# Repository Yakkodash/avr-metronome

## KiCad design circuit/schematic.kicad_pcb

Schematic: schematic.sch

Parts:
C1: 100n; C_0603_1608Metric
C2: 0.47u; C_0603_1608Metric_Pad1.05x0.95mm_HandSolder
C3, C10, C11: 220u; CP_Radial_D8.0mm_P3.50mm
C4, C6, C13, C14, C15, C16, C17, C18, C19: 0.1u; C_0603_1608Metric_Pad1.05x0.95mm_HandSolder
C5: 100u; CP_Radial_D8.0mm_P3.50mm
C7: 470p; C_0603_1608Metric_Pad1.05x0.95mm_HandSolder
C8, C9: 22p; C_0603_1608Metric_Pad1.05x0.95mm_HandSolder
C12: 470u; CP_Radial_D8.0mm_P3.50mm
D1: 1N4007; D_DO-41_SOD81_P7.62mm_Horizontal
D2, D3, D4: LED; LED_D3.0mm
D5: 1N5819; D_DO-41_SOD81_P7.62mm_Horizontal
H1, H2, H3, H4: MountingHole; MountingHole_3.2mm_M3
J1: Conn_01x02_Male; PinHeader_1x02_P2.54mm_Vertical
J2: Conn_01x05_Male; PinHeader_1x05_P2.54mm_Vertical
J3: Conn_01x02_Female; PinHeader_1x02_P2.54mm_Vertical
J4: AudioJack3_SwitchTR; PinHeader_1x05_P2.54mm_Vertical
L1: 220u; L_10.4x10.4_H4.8
R1, R9: 5k; R_0603_1608Metric_Pad1.05x0.95mm_HandSolder
R2: 150; R_0603_1608Metric_Pad1.05x0.95mm_HandSolder
R3: 0.33; R_Axial_DIN0204_L3.6mm_D1.6mm_P7.62mm_Horizontal
R4, R5, R6: 510; R_0603_1608Metric_Pad1.05x0.95mm_HandSolder
R7: 20k; R_0603_1608Metric_Pad1.05x0.95mm_HandSolder
R8: 1.2k; R_0603_1608Metric_Pad1.05x0.95mm_HandSolder
R10: 3.6k; R_0603_1608Metric_Pad1.05x0.95mm_HandSolder
R11, R12: 4.7k; R_0603_1608Metric_Pad1.05x0.95mm_HandSolder
R13: 330; R_0603_1608Metric_Pad1.05x0.95mm_HandSolder
R14, R15, R16, R17, R18, R19, R20, R21, R22, R23, R24, R25: 10k; R_0603_1608Metric_Pad1.05x0.95mm_HandSolder
RV1: R_POT_Dual; Potentiometer_Alps_RK09L_Double_Vertical
RV2: 20k; Potentiometer_Bourns_3314G_Vertical
SW1: Rotary_Encoder_Switch; RotaryEncoder_Alps_EC11E-Switch_Vertical_H20mm_CircularMoun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
SW2: SW_Push; PinHeader_1x02_P2.54mm_Vertical
SW3, SW4: SW_Push; SW_PUSH_6mm_H5mm
U1: ATmega328-AU; TQFP-32_7x7mm_P0.8mm
U2: SSM2211S; SOIC-8_3.9x4.9mm_P1.27mm
U3: MC33063AD; SOIC-8_3.9x4.9mm_P1.27mm
U4: STP08CP05; SOIC-16_3.9x9.9mm_P1.27mm
U5: 74HC14; SOIC-14_3.9x8.7mm_P1.27mm
U6: CC56-12SRWA; CA56-12SRWA
Y1: 16M; Crystal_SMD_5032-2Pin_5.0x3.2mm_HandSoldering

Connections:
+5V: C3.1, C4.2, C12.1, C13.1, J2.2, L1.2, R1.2, R9.1, R10.1, R14.1, R15.1, R16.1, R17.1, R18.1, R19.1, U1.4, U1.6, U1.18, U2.6, U4.4, U4.16, U5.14 (VCC)
+9V: C5.1, D1.1 (K), R3.2, U3.6
AMP_SHUTDOWN: R1.1, U1.28, U2.1
BUTTON0: U1.1, U5.2
BUTTON1: U1.32, U5.4
BUTTON2: U1.31, U5.6
DIG0: U1.23, U6.12 (CC1)
DIG1: U1.24, U6.9 (CC2)
DIG2: U1.25, U6.8 (CC3)
DIG3: U1.26, U6.6 (CC4)
ENC_A: U1.13, U5.8
ENC_B: U1.12, U5.10
ENC_BUTTON: U1.11, U5.12
GND: C1.2, C3.2, C4.1, C5.2, C6.2, C7.2, C8.1, C9.2, C12.2, C13.2, C14.2, C15.2, C16.2, C17.2, C18.2, C19.2, D2.1 (K), D3.1 (K), D4.1 (K), D5.2, J1.1, J2.1, J4.S, R8.1, R11.2, R12.2, RV1.1, RV1.4, RV2.2, RV2.3, SW1.C, SW1.MP, SW1.S1, SW2.1, SW3.1, SW4.1, U1.3, U1.5, U1.21, U2.7, U3.4, U4.1, U4.13, U5.7 (GND)
NRST: J2.3, R9.2, U1.29
unnamed: C1.1, U1.20
unnamed: C2.1, R2.2
unnamed: C6.1, U2.2, U2.3
unnamed: C7.1, U3.3
unnamed: C8.2, U1.7, Y1.1
unnamed: C9.1, U1.8, Y1.2
unnamed: C10.1, R7.1, U2.5
unnamed: C10.2, RV1.3
unnamed: C11.1, U2.8
unnamed: C11.2, RV1.6
unnamed: C14.1, R20.2, U5.11
unnamed: C15.1, R21.1, U5.13
unnamed: C16.1, R22.1, U5.9
unnamed: C17.1, R23.1, U5.1
unnamed: C18.1, R24.1, U5.3
unnamed: C19.1, R25.2, U5.5
unnamed: D1.2 (A), J1.2
unnamed: D2.2 (A), R4.2
unnamed: D3.2 (A), R5.1
unnamed: D4.2 (A), R6.2
unnamed: D5.1, L1.1, U3.2
unnamed: J3.1, J4.RN
unnamed: J3.2, J4.TN
unnamed: J4.R, R12.1, RV1.5
unnamed: J4.T, R11.1, RV1.2
unnamed: R2.1, R7.2, U2.4
unnamed: R3.1, U3.1, U3.7, U3.8
unnamed: R4.1, U1.30
unnamed: R5.2, U1.9
unnamed: R6.1, U1.2
unnamed: R8.2, R10.2, U3.5
unnamed: R13.1, U4.15
unnamed: R13.2, RV2.1
unnamed: R14.2, R20.1, SW1.A
unnamed: R15.2, R21.2, SW1.S2
unnamed: R16.2, R22.2, SW1.B
unnamed: R17.2, R23.2, SW2.2
unnamed: R18.2, R24.2, SW3.2
unnamed: R19.2, R25.1, SW4.2
unnamed: U4.5, U6.11 (a)
unnamed: U4.6, U6.7 (b)
unnamed: U4.7, U6.4 (c)
unnamed: U4.8, U6.2 (d)
unnamed: U4.9, U6.1 (e)
unnamed: U4.10, U6.10 (f)
unnamed: U4.11, U6.5 (g)
unnamed: U4.12, U6.3 (DPX)
SOUND_OUT: C2.2, U1.10
SPI_MISO: J2.4, U1.16
SPI_MOSI: U1.15, U4.2
SPI_SCK: J2.5, U1.17, U4.3

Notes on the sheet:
27 1.2
MIDI OUT?
Speaker
3 1
6 4

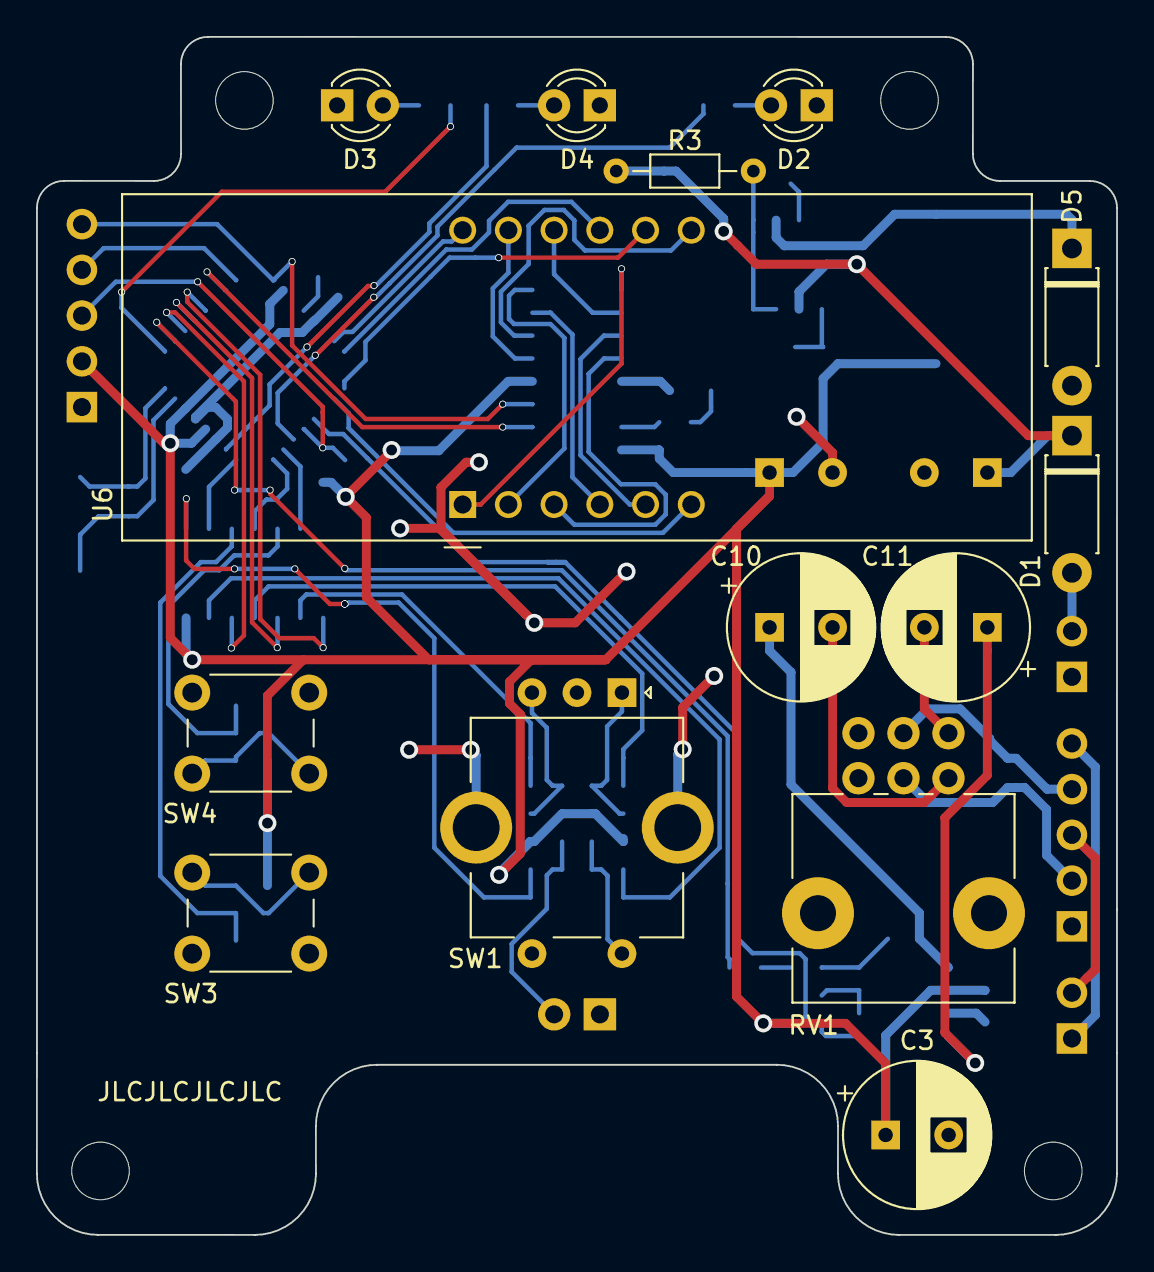
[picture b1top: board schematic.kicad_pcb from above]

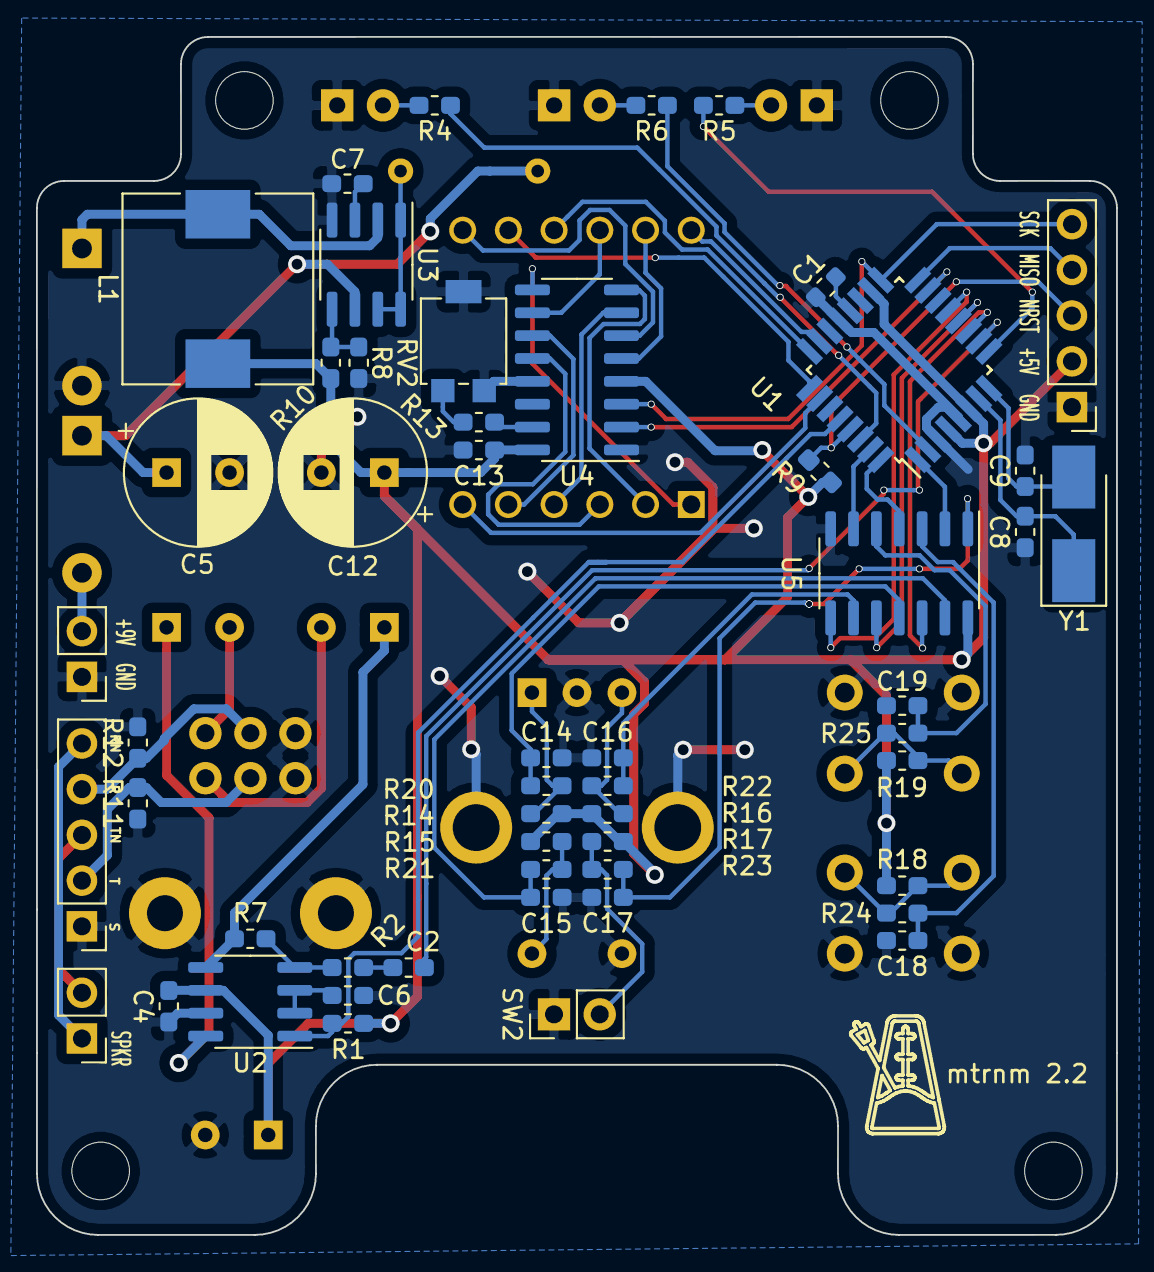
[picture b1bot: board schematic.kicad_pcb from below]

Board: 2 copper layers, 60.0 x 66.6 mm, 71 parts (53 on the bottom side), 66 nets.

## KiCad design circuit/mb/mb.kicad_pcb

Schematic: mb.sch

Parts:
BT1: 9V; PinHeader_1x02_P2.54mm_Vertical
C1, C2: 22p; C_Disc_D3.8mm_W2.6mm_P2.50mm
C3: 47u; CP_Radial_D4.0mm_P2.00mm
C4: 100u; CP_Radial_D4.0mm_P2.00mm
C5: 2200u; CP_Axial_L29.0mm_D13.0mm_P35.00mm_Horizontal
D1: 1N4001; D_DO-35_SOD27_P7.62mm_Horizontal
J1, J10: Conn_01x03_Male; PinHeader_1x03_P2.54mm_Vertical
J2: Conn_01x02_Male; PinHeader_1x02_P2.54mm_Vertical
J3: Barrel_Jack_Switch; PinHeader_1x03_P2.54mm_Vertical
J4: Conn_02x03_Odd_Even; PinHeader_2x03_P2.54mm_Vertical
J5, J6, J7: Conn_01x04_Male; PinHeader_1x04_P2.54mm_Vertical
J8, J9: Conn_01x05_Male; PinHeader_1x05_P2.54mm_Vertical
LS1: Speaker; PinHeader_1x02_P2.54mm_Vertical
Q1: BC337; TO-92_Inline_Wide
R1: 2.2k; R_Axial_DIN0204_L3.6mm_D1.6mm_P7.62mm_Horizontal
R2, R3: 100k; R_Axial_DIN0204_L3.6mm_D1.6mm_P7.62mm_Horizontal
R4: 10; R_Axial_DIN0204_L3.6mm_D1.6mm_P7.62mm_Horizontal
R5: 1k; R_Axial_DIN0204_L3.6mm_D1.6mm_P7.62mm_Horizontal
R6: 10k; R_Axial_DIN0204_L3.6mm_D1.6mm_P7.62mm_Horizontal
R7, R13: 0; R_Axial_DIN0204_L3.6mm_D1.6mm_P5.08mm_Horizontal
R8, R9, R10, R14, R16, R19, R22, R24: 0; R_Axial_DIN0204_L3.6mm_D1.6mm_P7.62mm_Horizontal
R11, R12, R15, R17, R18, R20, R21, R25: 0; R_Axial_DIN0207_L6.3mm_D2.5mm_P10.16mm_Horizontal
R23: 0; R_Axial_DIN0309_L9.0mm_D3.2mm_P20.32mm_Horizontal
R26: 0; R_Axial_DIN0309_L9.0mm_D3.2mm_P25.40mm_Horizontal
SW1, SW2: SW_SPDT; PinHeader_1x03_P2.54mm_Vertical
U1: ATmega328P-PU; DIP-28_W7.62mm_Socket
U2: L7805; TO-220-3_Vertical
Y1: 16M; Resonator-2Pin_W10.0mm_H5.0mm

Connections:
+5V: C5.1, J4.2, J8.5, J9.5, J10.1, R4.2, R10.1, R10.2, R11.2, R14.1, R14.2, R16.1, R16.2, U1.20 (AVCC), U1.21 (AREF), U2.3 (OUT)
+9V: C4.1, SW2.2 (B), U2.1 (IN)
BUTTON0: J5.3, U1.5 (PD3)
BUTTON1: J5.2, U1.4 (PD2)
BUTTON2: J5.1, R13.1
DIG0: J6.3, U1.24 (PC1)
DIG1: J6.2, U1.25 (PC2)
DIG2: J6.1, U1.26 (PC3)
DIG3: J6.4, U1.23 (PC0)
ENC_A: J8.2, U1.15 (PB1)
ENC_B: J8.3, U1.14 (PB0)
ENC_BUTTON: J5.4, R12.1
GND: BT1.2 (-), C1.1, C2.1, C3.2, C4.2, C5.2, J3.1, J4.6, J7.4, J8.4, J9.2, Q1.3 (E), R3.2, R6.1, R17.1, R17.2, R19.1, R19.2, R20.1, R20.2, R21.1, R21.2, SW1.1 (A), U1.8 (GND), U1.22 (GND), U2.2 (GND)
LED0: R22.1, U1.2 (PD0)
LED1: R15.1, R24.1
LED2: R26.1, U1.11 (PD5)
NRST: J4.5, J10.2, R7.1, R7.2, U1.1 (~RESET~/PC6)
unnamed: BT1.1 (+), J3.3
unnamed: C1.2, U1.9 (XTAL1/PB6), Y1.1
unnamed: C2.2, U1.10 (XTAL2/PB7), Y1.2
unnamed: C3.1, R5.1
unnamed: D1.1, J1.1, J2.1, LS1.1, Q1.1 (C), R2.1
unnamed: D1.2, J1.2, J2.2, SW1.3 (C)
unnamed: J1.3, R4.1
unnamed: J3.2, SW2.3 (C)
unnamed: J7.1, R22.2
unnamed: J7.2, R24.2
unnamed: J7.3, R25.1
unnamed: J9.3, R9.1
unnamed: J10.3, R6.2
unnamed: LS1.2, SW1.2 (B)
unnamed: Q1.2 (B), R1.1, R2.2, R3.1
unnamed: R8.2, U1.17 (PB3)
unnamed: R11.1, U1.7 (VCC)
unnamed: R12.2, U1.13 (PD7)
unnamed: R13.2, U1.3 (PD1)
unnamed: R15.2, U1.6 (PD4)
unnamed: R5.2, R18.1
unnamed: R18.2, U1.28 (PC5)
unnamed: R23.2, U1.27 (PC4)
unnamed: R25.2, R26.2
SOUND_OUT: R1.2, U1.12 (PD6)
SPI_MISO: J4.1, U1.18 (PB4)
SPI_MOSI: J4.4, J9.1, R8.1
SPI_NSS: R9.2, U1.16 (PB2)
SPI_SCK: J4.3, J9.4, U1.19 (PB5)
SWITCH0: J8.1, R23.1

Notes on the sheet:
Audio jack Must be isolated from the chassis

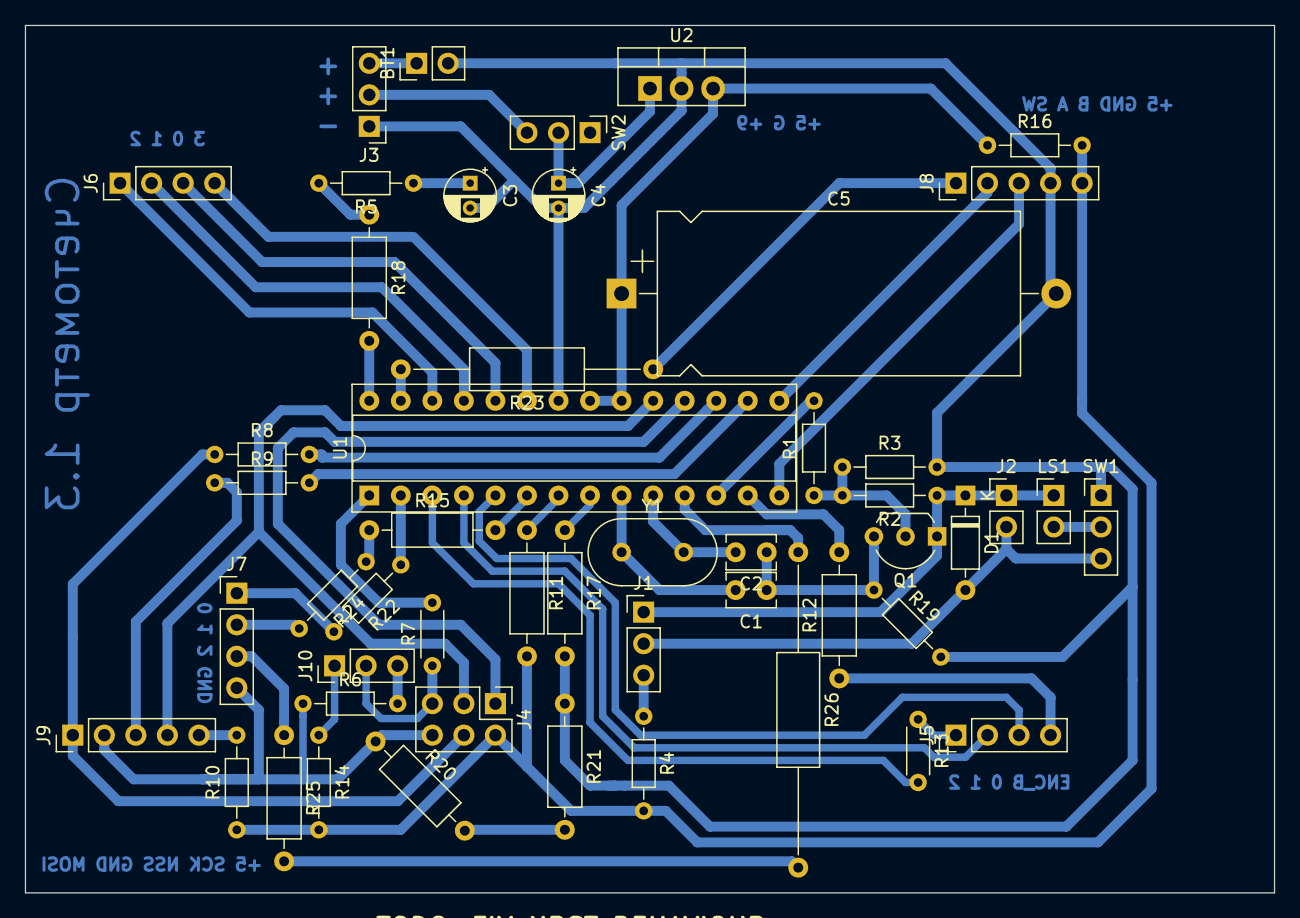
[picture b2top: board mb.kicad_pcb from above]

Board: 2 copper layers, 100.6 x 69.9 mm, 50 parts (0 on the bottom side), 47 nets.

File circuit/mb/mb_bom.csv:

"Позиция";"Обозначение";"Корпус";"Количество";"Значение";"Поставщик и справка";
1;"R8,R9,R16,R10,R19,R22,R24,R14";"R_Axial_DIN0204_L3.6mm_D1.6mm_P7.62mm_Horizontal";8;"0";;;
2;"U1";"DIP-28_W7.62mm_Socket";1;"ATmega328P-PU";;;
3;"J4";"PinHeader_2x03_P2.54mm_Vertical";1;"Conn_02x03_Odd_Even";;;
4;"SW2,SW1";"PinHeader_1x03_P2.54mm_Vertical";2;"SW_SPDT";;;
5;"Y1";"Resonator-2Pin_W10.0mm_H5.0mm";1;"16M";;;
6;"Q1";"TO-92_Inline_Wide";1;"BC337";;;
7;"BT1";"PinHeader_1x02_P2.54mm_Vertical";1;"9V";;;
8;"J1,J10";"PinHeader_1x03_P2.54mm_Vertical";2;"Conn_01x03_Male";;;
9;"J2";"PinHeader_1x02_P2.54mm_Vertical";1;"Conn_01x02_Male";;;
10;"J3";"PinHeader_1x03_P2.54mm_Vertical";1;"Barrel_Jack_Switch";;;
11;"J5,J6,J7";"PinHeader_1x04_P2.54mm_Vertical";3;"Conn_01x04_Male";;;
12;"J8,J9";"PinHeader_1x05_P2.54mm_Vertical";2;"Conn_01x05_Male";;;
13;"R1";"R_Axial_DIN0204_L3.6mm_D1.6mm_P7.62mm_Horizontal";1;"2.2k";;;
14;"R2,R3";"R_Axial_DIN0204_L3.6mm_D1.6mm_P7.62mm_Horizontal";2;"100k";;;
15;"R4";"R_Axial_DIN0204_L3.6mm_D1.6mm_P7.62mm_Horizontal";1;"10";;;
16;"R5";"R_Axial_DIN0204_L3.6mm_D1.6mm_P7.62mm_Horizontal";1;"1k";;;
17;"LS1";"PinHeader_1x02_P2.54mm_Vertical";1;"Speaker";;;
18;"U2";"TO-220-3_Vertical";1;"L7805";;;
19;"R6";"R_Axial_DIN0204_L3.6mm_D1.6mm_P7.62mm_Horizontal";1;"10k";;;
20;"R11,R18,R12,R15,R17,R20,R21,R25";"R_Axial_DIN0207_L6.3mm_D2.5mm_P10.16mm_Horizontal";8;"0";;;
21;"D1";"D_DO-35_SOD27_P7.62mm_Horizontal";1;"1N4001";;;
22;"R23";"R_Axial_DIN0309_L9.0mm_D3.2mm_P20.32mm_Horizontal";1;"0";;;
23;"C5";"CP_Axial_L29.0mm_D13.0mm_P35.00mm_Horizontal";1;"2200u";;;
24;"C3";"CP_Radial_D4.0mm_P2.00mm";1;"47u";;;
25;"C4";"CP_Radial_D4.0mm_P2.00mm";1;"100u";;;
26;"C1,C2";"C_Disc_D3.8mm_W2.6mm_P2.50mm";2;"22p";;;
27;"R7,R13";"R_Axial_DIN0204_L3.6mm_D1.6mm_P5.08mm_Horizontal";2;"0";;;
28;"R26";"R_Axial_DIN0309_L9.0mm_D3.2mm_P25.40mm_Horizontal";1;"0";;;

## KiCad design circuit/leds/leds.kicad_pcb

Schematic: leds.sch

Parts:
D1, D2, D3: LED; LED_D5.0mm
J1: Conn_01x04_Female; PinHeader_1x04_P2.54mm_Vertical
R1, R2, R3: 510; R_Axial_DIN0204_L3.6mm_D1.6mm_P7.62mm_Horizontal

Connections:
GND: D1.1 (K), D2.1 (K), D3.1 (K), J1.4
LED0: J1.1, R1.2
LED1: J1.2, R2.2
LED2: J1.3, R3.2
unnamed: D1.2 (A), R1.1
unnamed: D2.2 (A), R2.1
unnamed: D3.2 (A), R3.1

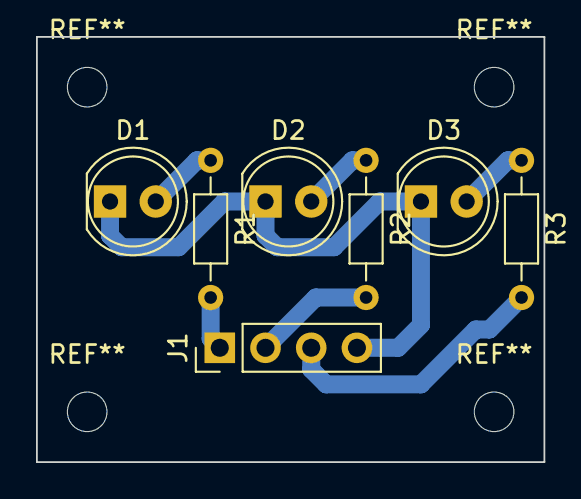
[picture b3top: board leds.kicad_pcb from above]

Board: 2 copper layers, 28.2 x 23.6 mm, 7 parts (0 on the bottom side), 7 nets.

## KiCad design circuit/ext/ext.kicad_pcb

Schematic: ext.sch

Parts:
C1, C2, C3, C4, C5, C6: 0.1u; C_Disc_D4.3mm_W1.9mm_P5.00mm
J1: Conn_01x04_Female; PinSocket_1x04_P2.54mm_Vertical
J2: Conn_01x03_Female; PinSocket_1x03_P2.54mm_Vertical
J3: Conn_01x05_Female; PinSocket_1x05_P2.54mm_Vertical
R1, R2, R3, R4, R5, R6, R7, R8, R9, R10, R11, R12: 10k; R_Axial_DIN0204_L3.6mm_D1.6mm_P7.62mm_Horizontal
R13, R14, R16: 0; R_Axial_DIN0204_L3.6mm_D1.6mm_P5.08mm_Horizontal
R15: 0; R_Axial_DIN0207_L6.3mm_D2.5mm_P15.24mm_Horizontal
R17: 0; R_Axial_DIN0207_L6.3mm_D2.5mm_P7.62mm_Horizontal
R18, R19, R20, R21, R22: 0; R_Axial_DIN0204_L3.6mm_D1.6mm_P7.62mm_Horizontal
RV1: 25k; Potentiometer_Alps_RK09K_Single_Vertical
SW1: Rotary_Encoder_Switch; RotaryEncoder_Alps_EC11E-Switch_Vertical_H20mm_CircularMoun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
SW2, SW4: SW_Push; SW_PUSH_6mm_H5mm
SW3: SW_Push; PinSocket_1x02_P2.54mm_Vertical
SW5: SW_SPDT; PinSocket_1x03_P2.54mm_Vertical
U1: 74HC14; DIP-14_W7.62mm_Socket

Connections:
+5V: J3.1, R1.1, R2.1, R3.1, R4.1, R5.1, R6.1, R13.1, R13.2, R14.1, R14.2, R16.1, R16.2, SW5.3 (C), U1.14 (VCC)
BUTTON0: J1.3, U1.8
BUTTON1: J1.2, U1.10
BUTTON2: J1.1, U1.12
ENC_A: J3.4, R19.2
ENC_B: J3.3, U1.4
ENC_BUTTON: J1.4, U1.6
GND: C1.2, C2.2, C3.2, C4.1, C5.2, C6.2, J3.2, SW1.C, SW1.S1, SW2.1, SW3.1, SW4.1, SW5.1 (A), U1.7 (GND)
unnamed: C1.1, R11.2, U1.1
unnamed: C2.1, R12.1, R22.2
unnamed: C3.1, R7.1, U1.3
unnamed: C4.2, R8.2, R20.2
unnamed: C5.1, R9.1, R17.2
unnamed: C6.1, R10.1, R18.2
unnamed: J2.1, RV1.1
unnamed: J2.2, RV1.2
unnamed: J2.3, RV1.3
unnamed: R1.2, R11.1, SW1.A
unnamed: R3.2, R7.2, SW1.B
unnamed: R4.2, R8.1, SW2.2
unnamed: R5.2, R9.2, SW3.2
unnamed: R6.2, R10.2, SW4.2
unnamed: R2.2, R12.2, SW1.S2
unnamed: R15.1, SW5.2 (B)
unnamed: R17.1, U1.11
unnamed: R18.1, U1.13
unnamed: R19.1, U1.2
unnamed: R20.1, R21.2
unnamed: R21.1, U1.9
unnamed: R22.1, U1.5
SWITCH0: J3.5, R15.2

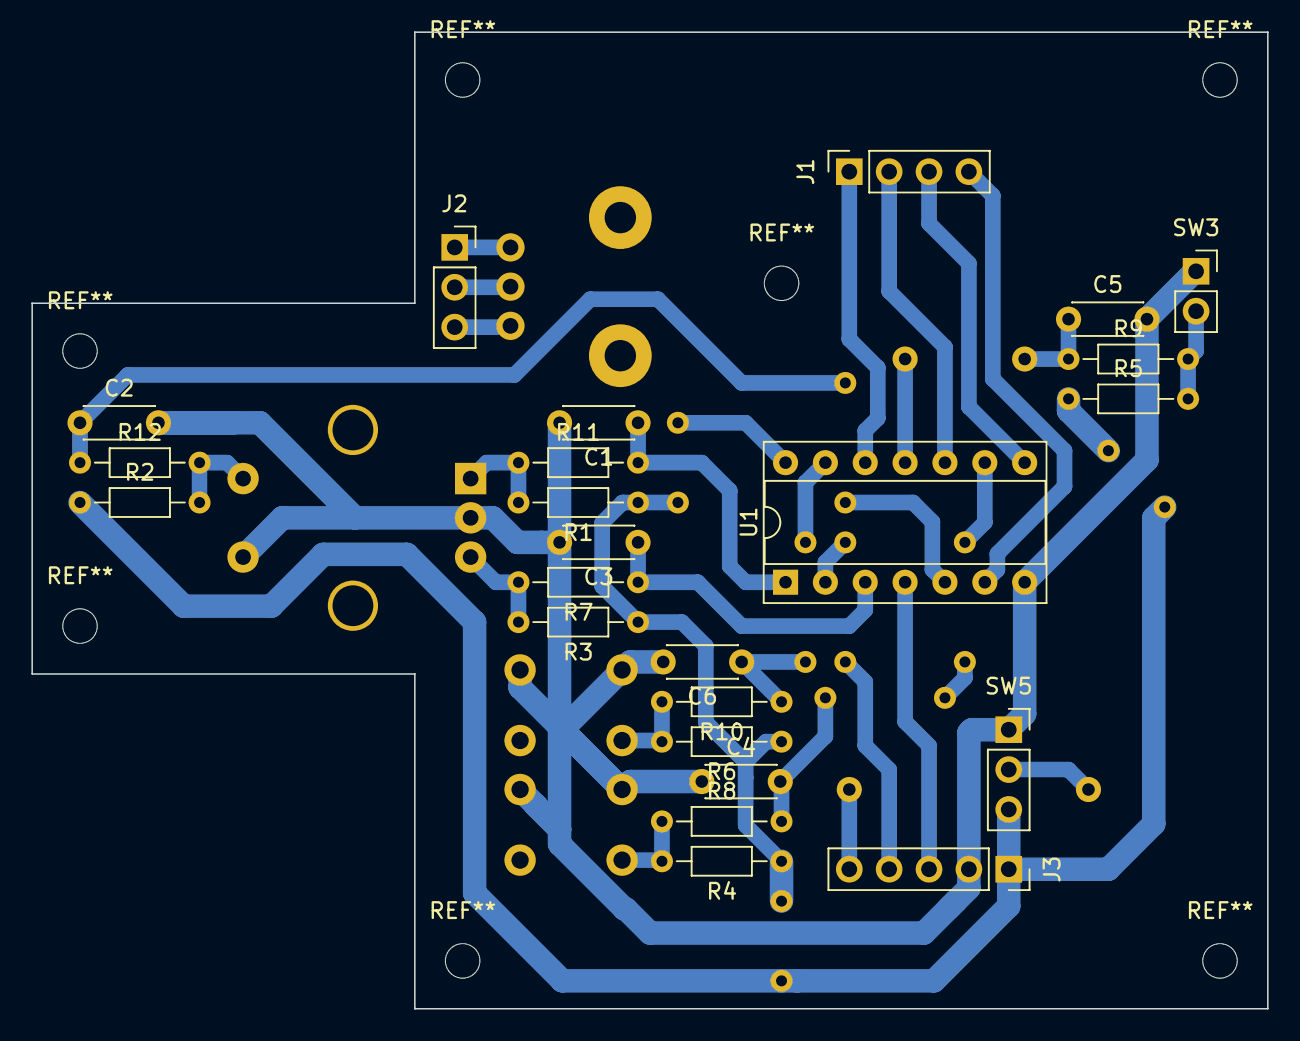
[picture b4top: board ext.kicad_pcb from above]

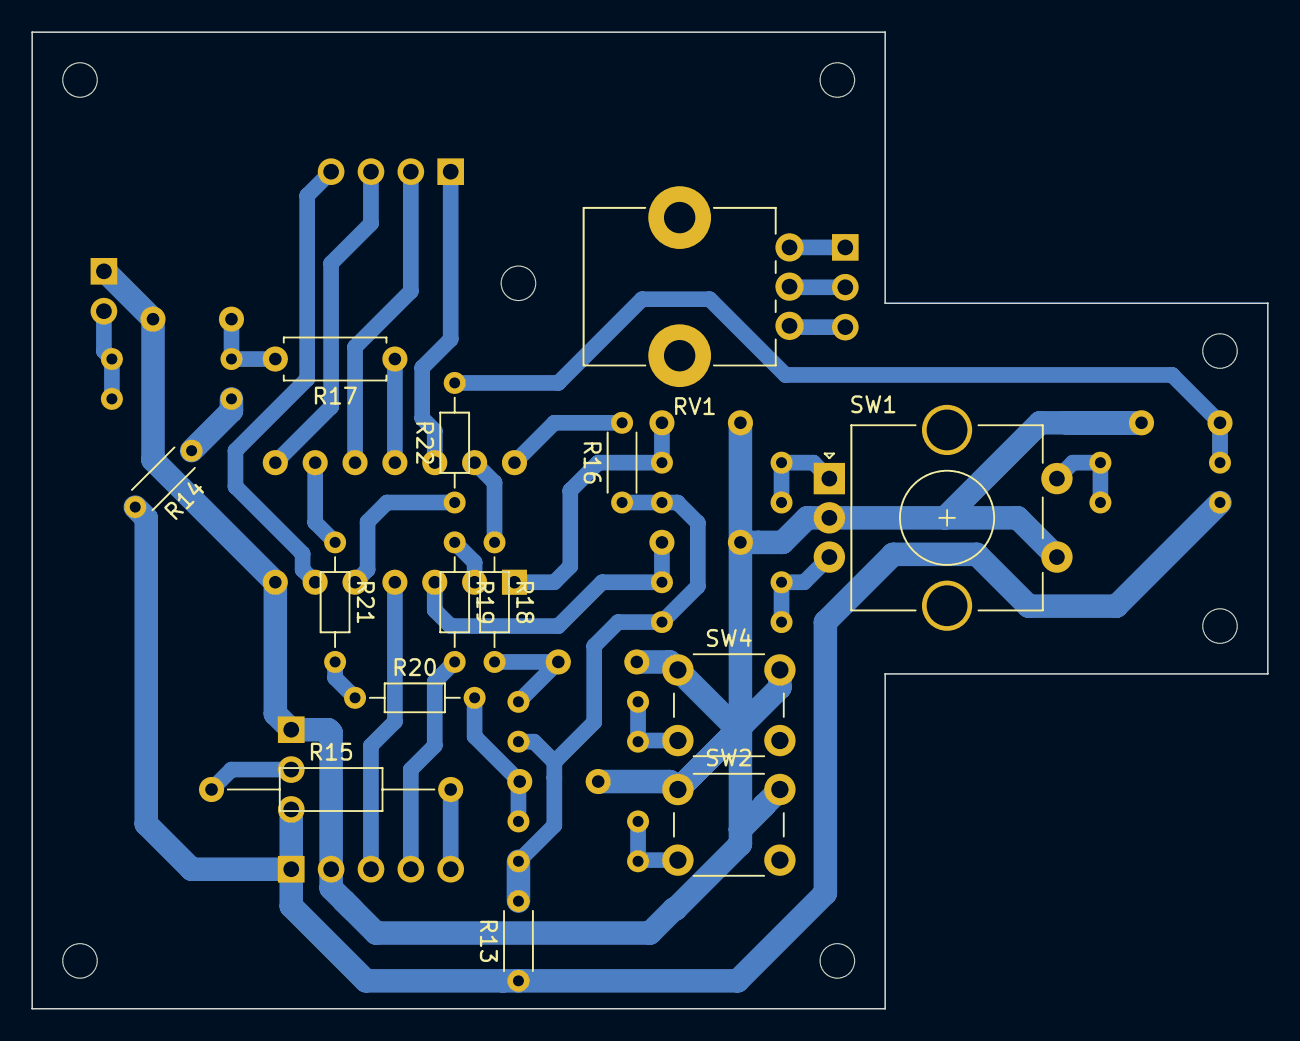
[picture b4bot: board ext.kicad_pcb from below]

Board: 2 copper layers, 78.7 x 62.2 mm, 38 parts (14 on the bottom side), 31 nets.

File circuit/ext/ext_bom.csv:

"Позиция";"Обозначение";"Корпус";"Количество";"Значение";"Поставщик и справка";
1;"REF**,REF**,REF**,REF**,REF**,REF**,REF**";"MountingHole_2.2mm_M2";7;"MountingHole_2.2mm_M2";;;
2;"C1,C2,C3,C4,C5,C6";"C_Disc_D4.3mm_W1.9mm_P5.00mm";6;"0.1u";;;
3;"J3";"PinSocket_1x05_P2.54mm_Vertical";1;"Conn_01x05_Female";;;
4;"R1,R2,R3,R4,R5,R6,R7,R8,R9,R10,R11,R12";"R_Axial_DIN0204_L3.6mm_D1.6mm_P7.62mm_Horizontal";12;"10k";;;
5;"U1";"DIP-14_W7.62mm_Socket";1;"74HC14";;;
6;"RV1";"Potentiometer_Alps_RK09K_Single_Vertical";1;"25k";;;
7;"SW1";"RotaryEncoder_Alps_EC11E-Switch_Vertical_H20mm_CircularMountingHoles";1;"Rotary_Encoder_Switch";;;
8;"SW2,SW4";"SW_PUSH_6mm_H5mm";2;"SW_Push";;;
9;"SW3";"PinSocket_1x02_P2.54mm_Vertical";1;"SW_Push";;;
10;"SW5";"PinSocket_1x03_P2.54mm_Vertical";1;"SW_SPDT";;;
11;"J2";"PinSocket_1x03_P2.54mm_Vertical";1;"Conn_01x03_Female";;;
12;"R13,R14,R16";"R_Axial_DIN0204_L3.6mm_D1.6mm_P5.08mm_Horizontal";3;"0";;;
13;"R18,R19,R20,R21,R22";"R_Axial_DIN0204_L3.6mm_D1.6mm_P7.62mm_Horizontal";5;"0";;;
14;"R17";"R_Axial_DIN0207_L6.3mm_D2.5mm_P7.62mm_Horizontal";1;"0";;;
15;"R15";"R_Axial_DIN0207_L6.3mm_D2.5mm_P15.24mm_Horizontal";1;"0";;;
16;"J1";"PinSocket_1x04_P2.54mm_Vertical";1;"Conn_01x04_Female";;;

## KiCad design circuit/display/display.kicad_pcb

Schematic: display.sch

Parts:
J1: Conn_01x05_Male; PinHeader_1x05_P2.54mm_Vertical
J2: Conn_01x04_Male; PinHeader_1x04_P2.54mm_Vertical
R1: 0; R_Axial_DIN0204_L3.6mm_D1.6mm_P7.62mm_Horizontal
R2, R3: 0; R_Axial_DIN0207_L6.3mm_D2.5mm_P10.16mm_Horizontal
R4, R5, R6, R7: 330; R_Axial_DIN0204_L3.6mm_D1.6mm_P7.62mm_Horizontal
U1: 74HC595; DIP-16_W7.62mm_Socket
U2: CC56-12SRWA; CA56-12SRWA

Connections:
+5V: J1.1, U1.10 (~SRCLR), U1.16 (VCC)
DIG0: J2.2, R4.1
DIG1: J2.3, R5.1
DIG2: J2.4, R6.1
DIG3: J2.1, R7.1
GND: J1.4, U1.8 (GND), U1.13 (~OE)
unnamed: R1.1, U2.7 (b)
unnamed: R1.2, U1.1 (QB)
unnamed: R2.1, U2.10 (f)
unnamed: R2.2, U1.5 (QF)
unnamed: R3.1, U2.5 (g)
unnamed: R3.2, U1.6 (QG)
unnamed: R4.2, U2.12 (CC1)
unnamed: R5.2, U2.9 (CC2)
unnamed: R6.2, U2.8 (CC3)
unnamed: R7.2, U2.6 (CC4)
unnamed: U1.2 (QC), U2.4 (c)
unnamed: U1.3 (QD), U2.2 (d)
unnamed: U1.4 (QE), U2.1 (e)
unnamed: U1.7 (QH), U2.3 (DPX)
unnamed: U1.15 (QA), U2.11 (a)
SPI_MOSI: J1.5, U1.14 (SER)
SPI_NSS: J1.3, U1.12 (RCLK)
SPI_SCK: J1.2, U1.11 (SRCLK)

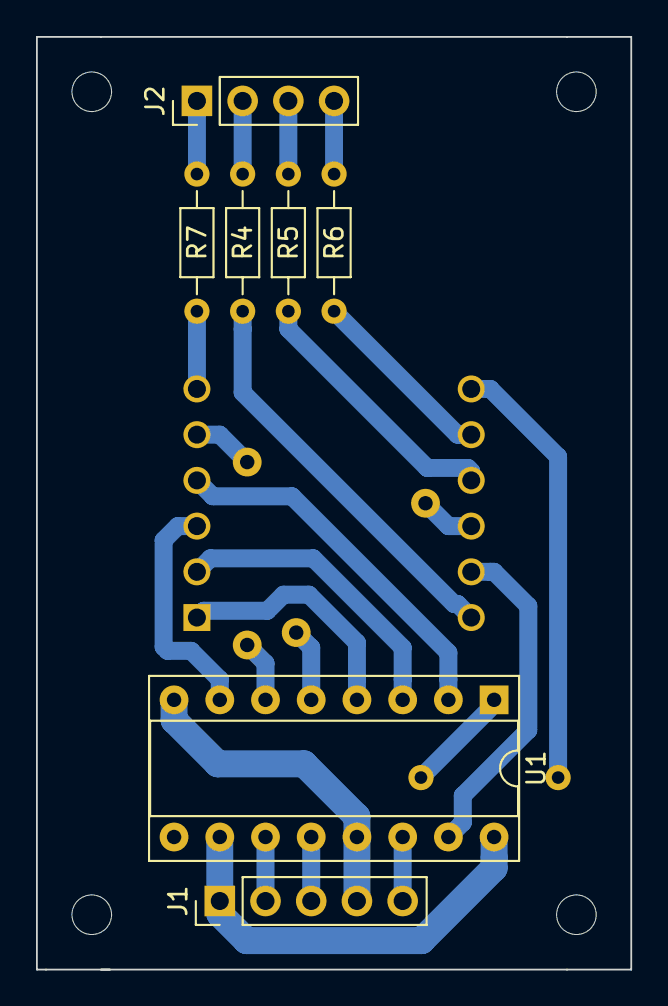
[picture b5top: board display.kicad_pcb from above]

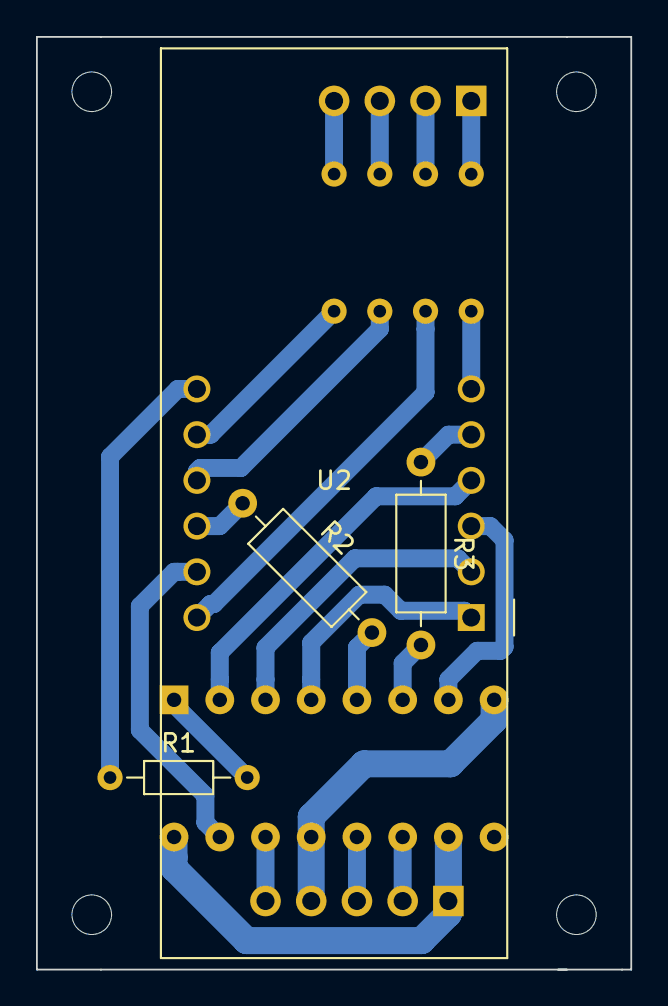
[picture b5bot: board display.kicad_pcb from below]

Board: 2 copper layers, 33.0 x 51.8 mm, 11 parts (4 on the bottom side), 24 nets.

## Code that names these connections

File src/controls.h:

#pragma once

#include <avr/io.h>
#include <avr/interrupt.h>

#define CTRL_ENC_BTN_PORT_DIR DDRD
#define CTRL_ENC_BTN_PORT     PORTD
#define CTRL_ENC_BTN_PIN      PD7
#define CTRL_ENC_BTN_INPINS   PIND
#define CTRL_ENC_BTN_PCINT    PCINT23
#define CTRL_ENC_BTN_PCMSK    PCMSK2
#define CTRL_ENC_BTN_PCINT_V  PCINT2_vect

#define CTRL_ENC_ROT_PORT_DIR DDRB
#define CTRL_ENC_ROT_PORT     PORTB
#define CTRL_ENC_ROT_A_PIN    PB0
#define CTRL_ENC_ROT_B_PIN    PB1
#define CTRL_ENC_ROT_INPINS   PINB
#define CTRL_ENC_ROT_A_PCINT  PCINT0
#define CTRL_ENC_ROT_B_PCINT  PCINT1
#define CTRL_ENC_ROT_PCMSK    PCMSK0
#define CTRL_ENC_ROT_PCINT_V  PCINT0_vect

#define CTRL_SWT_PORT_DIR DDRC
#define CTRL_SWT_PORT     PORTC
#define CTRL_SWT_PIN      PC4
#define CTRL_SWT_INPINS   PINC
#define CTRL_SWT_PCINT    PCINT12
#define CTRL_SWT_PCMSK    PCMSK1
#define CTRL_SWT_PCINT_V  PCINT1_vect

#define CTRL_BTN2_PORT_DIR  DDRD
#define CTRL_BTN2_PORT      PORTD
#define CTRL_BTN2_INPINS    PIND
#define CTRL_BTN2_PIN       PD1
#define CTRL_BTN2_PCINT     PCINT17
#define CTRL_BTN2_PCMSK     PCMSK2
#define CTRL_BTN2_PCINT_V   PCINT2_vect

#define CTRL_BTN1_PORT_DIR  DDRD
#define CTRL_BTN1_PORT      PORTD
#define CTRL_BTN1_INPINS    PIND
#define CTRL_BTN1_PIN       PD2
#define CTRL_BTN1_INT       INT0
#define CTRL_BTN1_LOGIC     ( _BV( ISC01 ) | _BV( ISC00 ) ) // rising edge
#define CTRL_BTN1_INT_V     INT0_vect

#define CTRL_BTN0_PORT_DIR  DDRD
#define CTRL_BTN0_PORT      PORTD
#define CTRL_BTN0_INPINS    PIND
#define CTRL_BTN0_PIN       PD3
#define CTRL_BTN0_INT       INT1
//#define CTRL_BTN0_LOGIC     ( _BV( ISC11 ) ) // falling edge
#define CTRL_BTN0_LOGIC     ( _BV( ISC11 ) | _BV( ISC10 ) ) // rising edge
#define CTRL_BTN0_INT_V     INT1_vect

extern volatile struct ctrl_s {
  void (*ctrl_enc_a_clbk)(void);
  void (*ctrl_enc_b_clbk)(void);
  void (*ctrl_enc_btn_clbk)(void);

  void (*ctrl_enc_a_btn_clbk)(void); // if encoder is rotated with button being hold
  void (*ctrl_enc_b_btn_clbk)(void);

  void (*ctrl_btn0_clbk)(void);
  void (*ctrl_btn1_clbk)(void);
  void (*ctrl_btn2_clbk)(void);

  void (*ctrl_btn012_clbk)(void);

  void (*ctrl_swt_on_clkb)(void);
  void (*ctrl_swt_off_clkb)(void);
} gl_ctrl_p;

void ctrl_init( void );

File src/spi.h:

// SPI for controlling 74hc595n chip
#pragma once

#include <avr/io.h>

#define SPI_PORT_DIR  DDRB

#define SPI_PORT      PORTB
#define SPI_NSS_PIN   PB2
#define SPI_MOSI_PIN  PB3
#define SPI_SCK_PIN   PB5

void spi_init( void );
void spi_transmit( uint8_t val );

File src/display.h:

#pragma once

#include <avr/io.h>

#define DISP_CS_DIR_PORT DDRC // character select
#define DISP_CS_PORT PORTC

#define DIG_NUM 4
#define DIG_NONE -1

#define DISP_DELAY_US 1000

static const uint8_t display_digs[DIG_NUM] = { PC1, PC2, PC3, PC0 };

void display_init( void );
void display_set_chars( char *data, uint8_t len );
void display_tick( void );

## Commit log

2018-12-22 Init commit
2018-12-31 Add support for 4 segment display, using SPI and 74hc595 chip
2018-12-31 Minor cleanup for display
2019-01-02 Remove itoa usage and remove unused SPI pin
2019-01-04 Add external controls support
2019-01-07 Add menu and utility timer (16us precision)
2019-01-07 Fix encoder first turn left bug
2019-01-07 Minor cleanup
2019-01-08 Add one more switch, eeprom settings saving on powerloss and one more menu
2019-01-08 Fix active BPM assignment
2019-01-10 Add KiCad schematic starter
2019-01-10 Add more components to the schematic
2019-01-10 Add more schematics, music notes and menus
2019-01-13 Migrate to bare atmega328p
2019-01-15 Refactor controls, menu and disable powerloss detection
2019-01-17 Some refactoring
2019-01-27 Update schematic
2019-11-04 Fix powerloss detection and add more schematics
2019-11-09 Add controls board schematic
2019-11-23 More schematics
2019-11-24 Update mb schematic
2019-11-26 Add dxf and bom
2019-11-30 Add tap tempo, improve EEPROM saving, add dxf's
2019-11-30 Reset cntdwn_en on sett reset
2020-06-01 Redo to one board
2020-10-07 Update board
2020-10-09 Change pot polarity
